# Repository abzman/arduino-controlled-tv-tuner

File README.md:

# arduino-controlled-tv-tuner
controlling a salvaged fm1236 tv tuner

TODO: change resistors to 1k (dim LEDs)
i2c bus shows devices at 0x60 and 0x43 with address select strapped 1-2

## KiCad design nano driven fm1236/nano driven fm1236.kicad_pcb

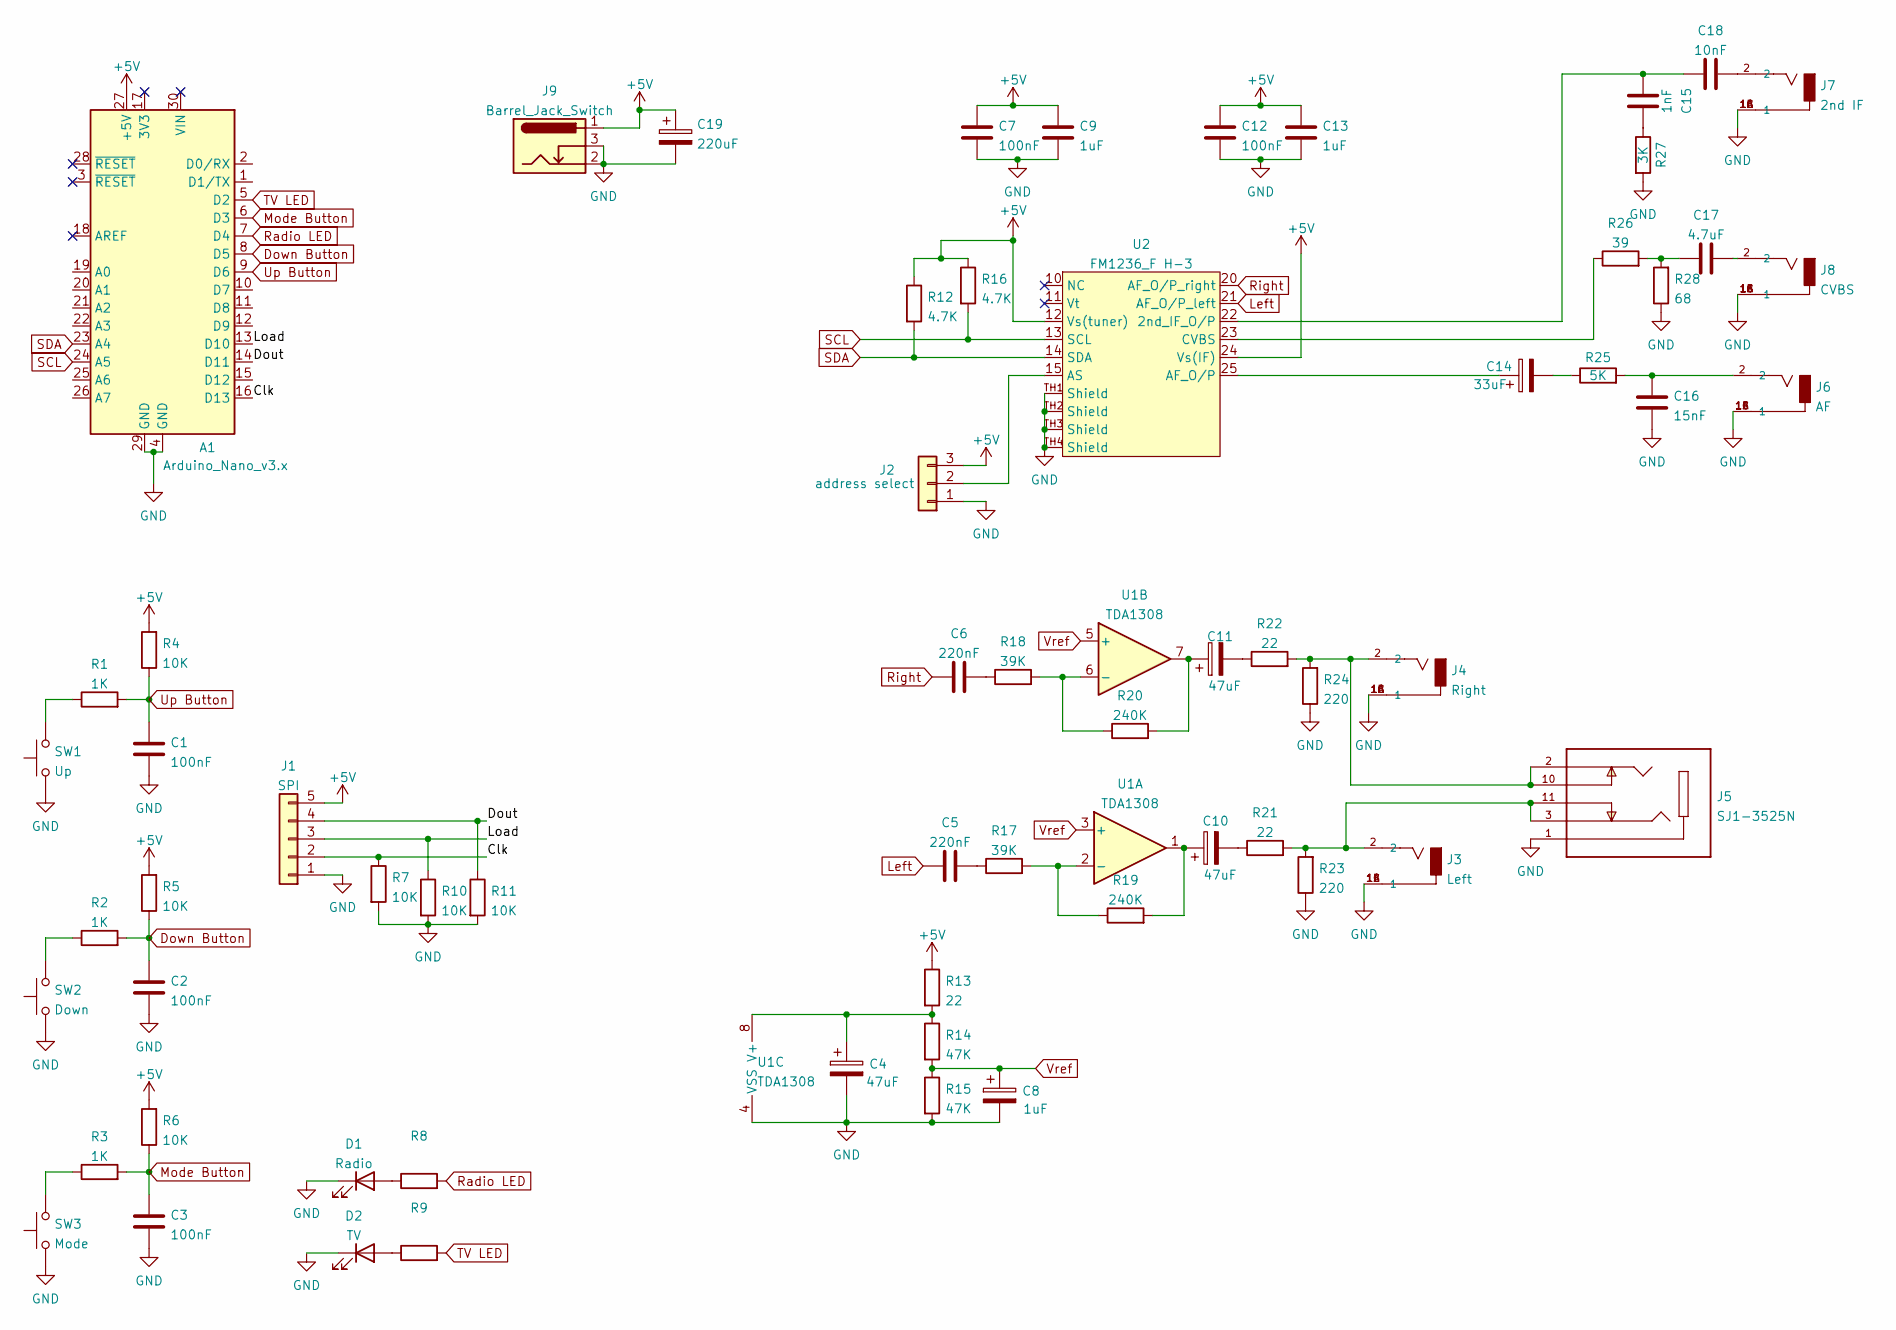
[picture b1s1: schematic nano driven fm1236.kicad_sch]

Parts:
A1: Arduino_Nano_v3.x; Arduino_Nano
C1, C2, C3, C7, C12: 100nF; C_0603_1608Metric
C4, C10, C11: 47uF; CP_Radial_D8.0mm_P3.50mm
C5, C6: 220nF; C_0603_1608Metric
C8: 1uF; CP_Radial_D5.0mm_P2.50mm
C9, C13: 1uF; C_0603_1608Metric
C14: 33uF; CP_Radial_D8.0mm_P3.50mm
C15: 1nF; C_0603_1608Metric
C16: 15nF; C_0603_1608Metric
C17: 4.7uF; C_0603_1608Metric
C18: 10nF; C_0603_1608Metric
C19: 220uF; C_Disc_D3.8mm_W2.6mm_P2.50mm
D1: Radio; LED_D3.0mm
D2: TV; LED_D3.0mm
J1: SPI; PinHeader_1x05_P2.54mm_Horizontal
J2: address select; SolderJumper-3_P1.3mm_Bridged12_Pad1.0x1.5mm_NumberLabels
J3: Left; CUI_RCJ-013; PART_REV B
J4: Right; CUI_RCJ-013; PART_REV B
J5: SJ1-3525N; CUI_SJ1-3525N; PARTREV 1.02
J6: AF; CUI_RCJ-013; PART_REV B
J7: 2nd IF; CUI_RCJ-013; PART_REV B
J8: CVBS; CUI_RCJ-013; PART_REV B
J9: Barrel_Jack_Switch; BarrelJack_Horizontal
R1, R2, R3: 1K; R_0603_1608Metric
R4, R5, R6, R7, R10, R11: 10K; R_0603_1608Metric
R8, R9: R_0603_1608Metric
R12, R16: 4.7K; R_0603_1608Metric
R13, R21, R22: 22; R_0603_1608Metric
R14, R15: 47K; R_0603_1608Metric
R17, R18: 39K; R_0603_1608Metric
R19, R20: 240K; R_0603_1608Metric
R23, R24: 220; R_0603_1608Metric
R25: 5K; R_0603_1608Metric
R26: 39; R_0603_1608Metric
R27: 3K; R_0603_1608Metric
R28: 68; R_0603_1608Metric
SW1: Up; SW_Tactile_SPST_Angled_PTS645Vx83-2LFS
SW2: Down; SW_Tactile_SPST_Angled_PTS645Vx83-2LFS
SW3: Mode; SW_Tactile_SPST_Angled_PTS645Vx83-2LFS
U1: TDA1308; SOIC-8_3.9x4.9mm_P1.27mm
U2: FM1236_F H-3

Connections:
+5V: A1.27 (+5V), C7.1, C9.1, C12.1, C13.1, C19.1, J1.5, J2.3, J9.1, R4.2, R5.2, R6.2, R12.1, R13.1, R16.1, U2.12 (Vs(tuner)), U2.24 (Vs(IF))
/Clk: A1.16 (D13), J1.2, R7.1
/Dout: A1.14 (D11), J1.4, R11.1
/Load: A1.13 (D10), J1.3, R10.1
Down Button: A1.8 (D5), C2.1, R2.2, R5.1
GND: A1.4 (GND), A1.29 (GND), C1.2, C2.2, C3.2, C4.2, C7.2, C8.2, C9.2, C12.2, C13.2, C16.2, C19.2, D1.1 (K), D2.1 (K), J1.1, J2.1, J3.1A (1), J3.1B (1), J3.1C (1), J4.1A (1), J4.1B (1), J4.1C (1), J5.1, J6.1A (1), J6.1B (1), J6.1C (1), J7.1A (1), J7.1B (1), J7.1C (1), J8.1A (1), J8.1B (1), J8.1C (1), J9.2, J9.3, R7.2, R10.2, R11.2, R15.2, R23.1, R24.1, R27.2, R28.1, SW1.1, SW2.1, SW3.1, U1.4 (VSS), U2.TH1 (Shield), U2.TH2 (Shield), U2.TH3 (Shield), U2.TH4 (Shield)
Left: C5.1, U2.21 (AF_O/P_left)
Mode Button: A1.6 (D3), C3.1, R3.2, R6.1
unnamed: C4.1, R13.2, R14.1, U1.8 (V+)
unnamed: C5.2, R17.1
unnamed: C6.2, R18.1
unnamed: C10.1, R19.2, U1.1
unnamed: C10.2, R21.1
unnamed: C11.1, R20.2, U1.7
unnamed: C11.2, R22.1
unnamed: C14.1, U2.25 (AF_O/P)
unnamed: C14.2, R25.1
unnamed: C15.1, C18.1, U2.22 (2nd_IF_O/P)
unnamed: C15.2, R27.1
unnamed: C16.1, J6.2, R25.2
unnamed: C17.1, R26.2, R28.2
unnamed: C17.2, J8.2
unnamed: C18.2, J7.2
unnamed: D1.2 (A), R8.1
unnamed: D2.2 (A), R9.1
unnamed: J2.2, U2.15 (AS)
unnamed: J3.2, J5.3, J5.11, R21.2, R23.2
unnamed: J4.2, J5.2, J5.10, R22.2, R24.2
unnamed: R1.1, SW1.2
unnamed: R2.1, SW2.2
unnamed: R3.1, SW3.2
unnamed: R17.2, R19.1, U1.2 (-)
unnamed: R18.2, R20.1, U1.6 (-)
unnamed: R26.1, U2.23 (CVBS)
Radio LED: A1.7 (D4), R8.2
Right: C6.1, U2.20 (AF_O/P_right)
SCL: A1.24 (A5), R16.2, U2.13 (SCL)
SDA: A1.23 (A4), R12.2, U2.14 (SDA)
TV LED: A1.5 (D2), R9.2
Up Button: A1.9 (D6), C1.1, R1.2, R4.1
Vref: C8.1, R14.2, R15.1, U1.3 (+), U1.5 (+)

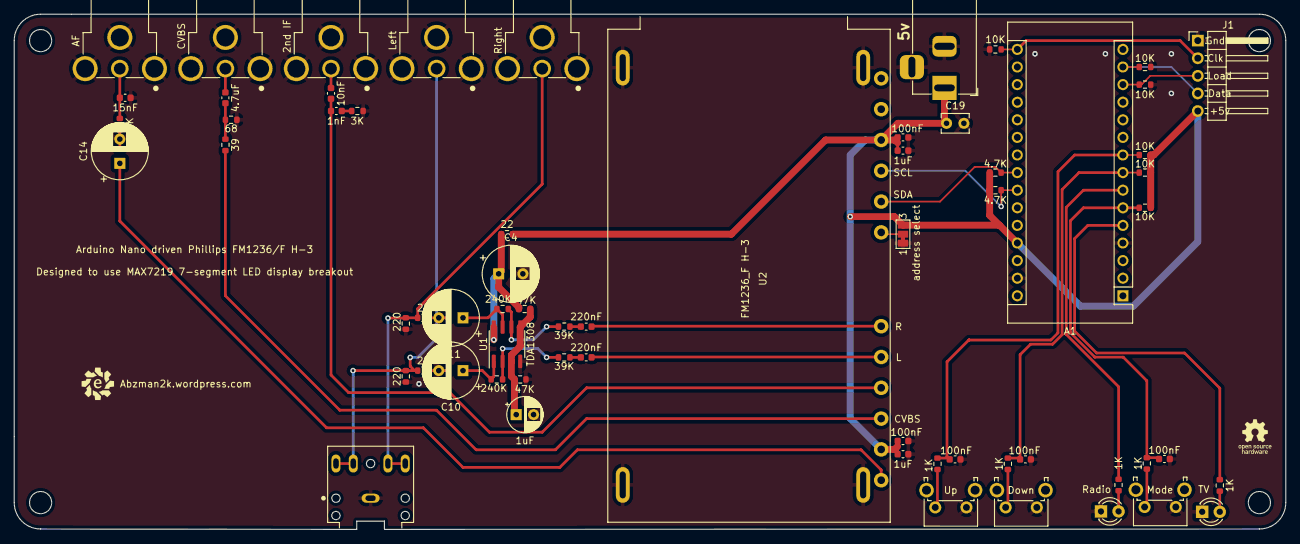
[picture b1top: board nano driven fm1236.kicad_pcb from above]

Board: 2 copper layers, 183.5 x 74.3 mm, 64 parts (0 on the bottom side), 41 nets.

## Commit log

2022-10-20 first rev schematic and board
2022-11-25 made gerbers and added gitignore for kicad
2022-11-26 added datasheet(s) notes and example for running the 7-segments
2023-01-03 added docs
